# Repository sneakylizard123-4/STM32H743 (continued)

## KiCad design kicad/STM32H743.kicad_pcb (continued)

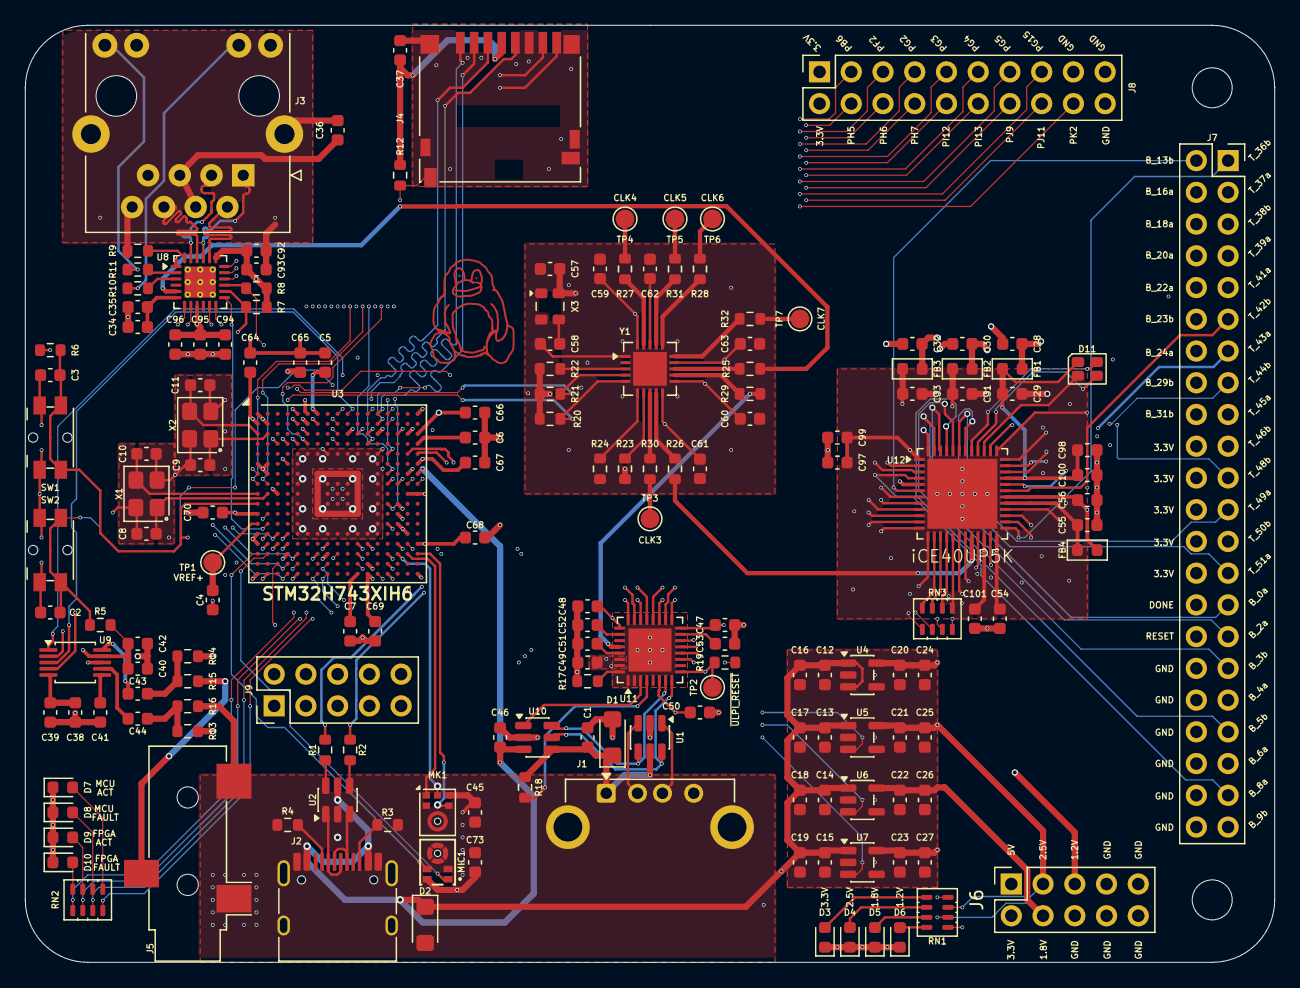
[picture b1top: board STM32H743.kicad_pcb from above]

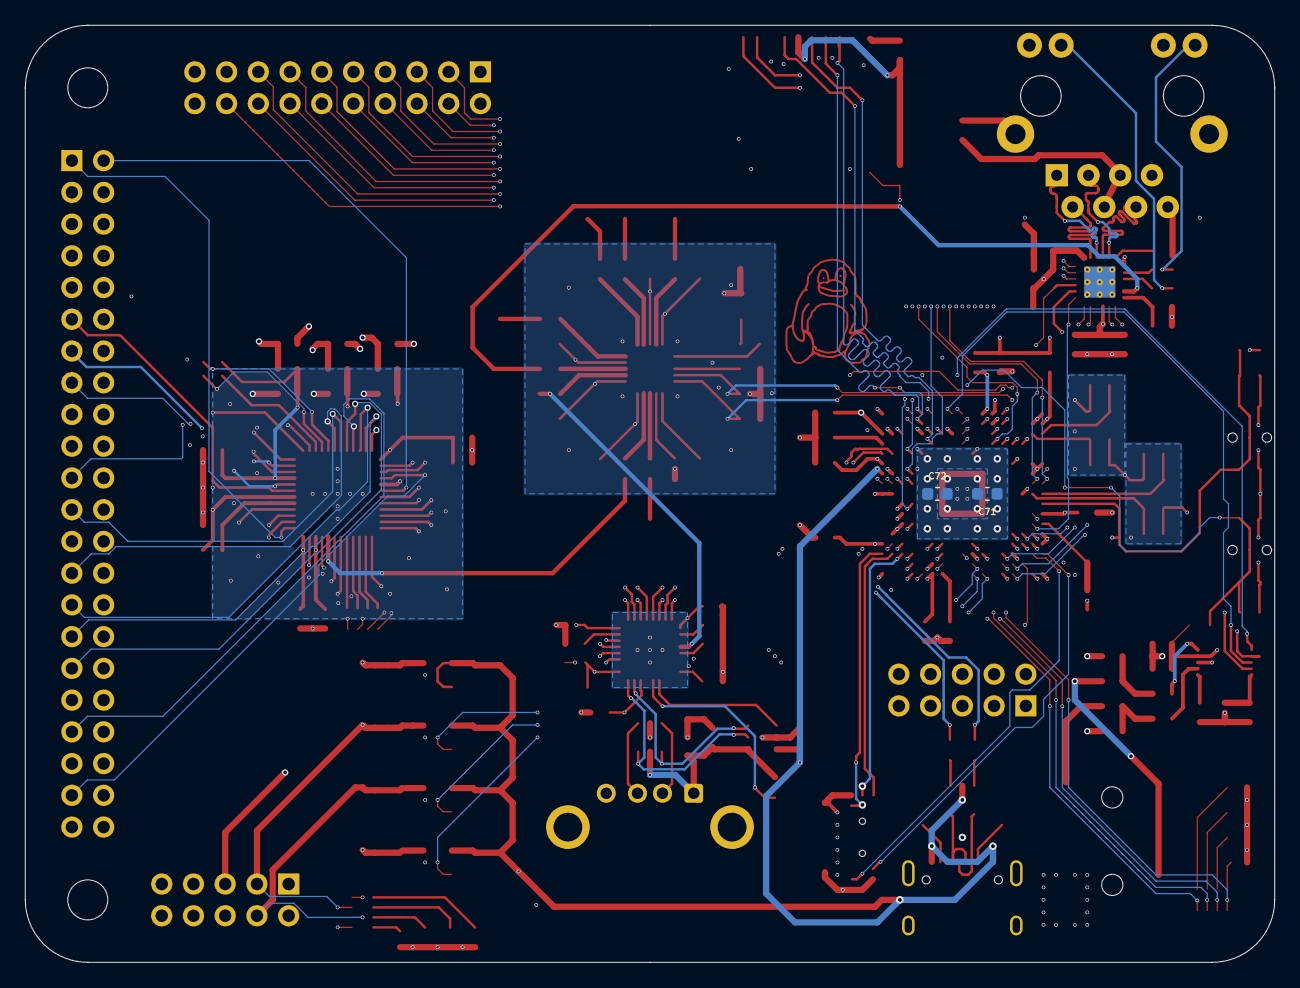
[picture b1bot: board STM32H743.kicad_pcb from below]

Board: 6 copper layers, 100.0 x 75.0 mm, 171 parts (2 on the bottom side), 196 nets.

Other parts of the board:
C73: 0.1uF; C_0603_1608Metric
MIC1: MMICT390200012; MIC-SMD_5P-L3.5-W2.7-TL_MMICT390200012
TP3, TP4, TP5, TP6, TP7: TestPoint; TestPoint_Pad_D1.5mm

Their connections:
+3.3V: C73.1, MIC1.5 (VDD); also elsewhere on the board
/Audio/DFSDM1.CKIN1: MIC1.4 (CLK); also elsewhere on the board
/Audio/DFSDM1.DATIN1: MIC1.1 (DATA); also elsewhere on the board
GND: C73.2, MIC1.3 (GND); also elsewhere on the board
unnamed 251: TP4.1 (1_1); also elsewhere on the board
unnamed 252: TP6.1 (1_1); also elsewhere on the board
unnamed 253: TP3.1 (1_1); also elsewhere on the board
unnamed 254: TP5.1 (1_1); also elsewhere on the board
unnamed 255: TP7.1 (1_1); also elsewhere on the board

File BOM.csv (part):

Comment,Designators,Footprint,Quantity,Supplier,Supplier Part,Unit Price (USD),Extended Price (USD),Supplier Link,Notes
"STM32H743XIH6","U3","TFBGA-265",1,"LCSC","C114407",25.9662,25.9662,"https://www.lcsc.com/product-detail/C114407.html","Main MCU, 480 MHz, 2 MB flash"
"ICE40UP5K-SG48I","U12","QFN-48-EP 7x7",1,"LCSC","C2678152",10.9007,10.9007,"https://www.lcsc.com/product-detail/C2678152.html","Substitute for obsolete ICE40UP5K-SG48ITR, same package"
"USB3300-EZK-TR","U11","QFN-32",1,"LCSC","C108383",1.4647,1.4647,"https://www.lcsc.com/product-detail/C108383.html","USB 2.0 HS ULPI PHY"
"LAN8742A-CZ-TR","U8","QFN-24-EP 4x4",1,"LCSC","C621424",1.4025,1.4025,"https://www.lcsc.com/product-detail/C621424.html","10/100 Ethernet PHY"
"CS4344-CZZR","U9","TSSOP-10",1,"LCSC","C8952",1.5154,1.5154,"https://www.lcsc.com/product-detail/C8952.html","Stereo I2S audio DAC"
"Si5351C-B-GM","Y1","QFN-20",1,"LCSC","C3608122",5.5527,5.5527,"https://www.lcsc.com/product-detail/C3608122.html","Clock generator"
"TLV75733PDBV","U4","SOT-23-5",1,"LCSC","C485517",0.2005,0.2005,"https://www.lcsc.com/product-detail/C485517.html","3.3 V LDO"
"TLV75725PDBV","U5","SOT-23-5",1,"LCSC","C2872563",0.2318,0.2318,"https://www.lcsc.com/product-detail/C2872563.html","2.5 V LDO"
"TLV75718PDBV","U6","SOT-23-5",1,"LCSC","C507270",0.2985,0.2985,"https://www.lcsc.com/product-detail/C507270.html","1.8 V LDO"
"TLV75712PDBV","U7","SOT-23-5",1,"LCSC","C1509296",0.3415,0.3415,"https://www.lcsc.com/product-detail/C1509296.html","1.2 V LDO"
"USBLC6-2SC6","U1 U2","SOT-23-6",2,"LCSC","C7519",0.1797,0.3594,"https://www.lcsc.com/product-detail/C7519.html","USB ESD protection"
"TPD3S014DBVR","U10","SOT-23-6",1,"LCSC","C87384",1.0327,1.0327,"https://www.lcsc.com/product-detail/C87384.html","USB-A host power switch and protection"
"ICS-43434","MK1","LGA-6 3.5x2.7",1,"LCSC","C5656610",4.6035,4.6035,"https://www.lcsc.com/product-detail/C5656610.html","PDM microphone"
"MMICT390200012","MIC1","LGA",1,"LCSC","C3171752",1.5613,1.5613,"https://www.lcsc.com/product-detail/C3171752.html","PDM microphone"
"CLMVC-FKA-CLBDGL7LBB79353","D11","PLCC-4",1,"Mouser","941-CLMVCFKACLBDGL7L",0.1400,0.1400,"https://www.mouser.ca/en/ProductDetail/Cree-LED/CLMVC-FKA-CL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","RGB LED, ABGR"
"0.1 uF 50 V X7R","C100 C101 C2 C3 C37 C39 C4 C42 C45 C46 C47 C48 C49 C50 C57 C59 C60 C61 C62 C63 C64 C65 C66 C67 C68 C69 C70 C71 C72 C73 C92 C93 C94 C95 C96 C97 C98 C99 C12 C13 C14 C15 C20 C21 C22 C23 C58","0603",47,"LCSC","C14663",0.0084,0.3948,"https://www.lcsc.com/product-detail/C14663.html","Includes both 0.1 uF and 100 nF values"
"10 uF 25 V X5R","C16 C17 C18 C19 C24 C25 C26 C27 C38 C41 C56","0603",11,"LCSC","C96446",0.0429,0.4719,"https://www.lcsc.com/product-detail/C96446.html",""
"1 uF 25 V X7R","C28 C29 C30 C31 C32 C33 C34 C40 C54 C55","0603",10,"LCSC","C29936",0.0177,0.1770,"https://www.lcsc.com/product-detail/C29936.html",""
"2.2 uF 25 V X7R","C5 C6 C7","0603",3,"LCSC","C99228",0.0567,0.1701,"https://www.lcsc.com/product-detail/C99228.html",""
"4.7 uF 25 V X5R","C51 C52 C53","0603",3,"LCSC","C69335",0.0428,0.1284,"https://www.lcsc.com/product-detail/C69335.html",""
"3.3 uF 25 V X5R","C43 C44","0603",2,"LCSC","C5360803",0.0142,0.0284,"https://www.lcsc.com/product-detail/C5360803.html",""
"22 nF 50 V X7R","C36","0603",1,"LCSC","C21122",0.0071,0.0071,"https://www.lcsc.com/product-detail/C21122.html",""
"470 pF 50 V C0G","C35","0603",1,"LCSC","C106211",0.0069,0.0069,"https://www.lcsc.com/product-detail/C106211.html",""
"12 pF 50 V C0G","C8 C10","0603",2,"LCSC","C38523",0.0112,0.0224,"https://www.lcsc.com/product-detail/C38523.html",""
"18 pF 50 V C0G","C9 C11","0603",2,"LCSC","C1647",0.0158,0.0316,"https://www.lcsc.com/product-detail/C1647.html",""
"47 uF 6.3 V X5R","C1","0603",1,"LCSC","C140782",0.1382,0.1382,"https://www.lcsc.com/product-detail/C140782.html","Rev A value was 120 uF, which does not fit 0603. This is below the USB 2.0 host 120 uF recommendation."
"12.1 k 1%","R9","0603",1,"LCSC","C22864",0.0015,0.0015,"https://www.lcsc.com/product-detail/C22864.html",""
"SMF12A","D1 D2","SOD-123FL",2,"LCSC","C19077506",0.0325,0.0650,"https://www.lcsc.com/product-detail/C19077506.html","TVS"
"1 k at 100 MHz ferrite","FB1 FB2 FB3 FB4","0603",4,"LCSC","C304312",0.0150,0.0600,"https://www.lcsc.com/product-detail/C304312.html",""
"Green LED","D3 D4 D5 D6","0603",4,"LCSC","C52675989",0.0035,0.0140,"https://www.lcsc.com/product-detail/C52675989.html",""
"Yellow LED","D7 D9","0603",2,"LCSC","C965802",0.0072,0.0144,"https://www.lcsc.com/product-detail/C965802.html",""
"Red LED","D8 D10","0603",2,"LCSC","C2286",0.0077,0.0154,"https://www.lcsc.com/product-detail/C2286.html",""
"1 k resistor array x4","RN1 RN2","0603x4",2,"LCSC","C20197",0.0104,0.0208,"https://www.lcsc.com/product-detail/C20197.html",""
"0 ohm resistor array x4","RN3","0603x4",1,"LCSC","C1952",0.0090,0.0090,"https://www.lcsc.com/product-detail/C1952.html",""
"22 ohm","R1 R2","0603",2,"LCSC","C23345",0.0017,0.0034,"https://www.lcsc.com/product-detail/C23345.html","USB series termination"
"330 ohm","R10 R11","0603",2,"LCSC","C23138",0.0020,0.0040,"https://www.lcsc.com/product-detail/C23138.html",""
"10 k","R5 R6 R7 R8 R12 R13 R14 R19 R22 R23 R24","0603",11,"LCSC","C25804",0.0022,0.0242,"https://www.lcsc.com/product-detail/C25804.html",""
"470 ohm","R15 R16","0603",2,"LCSC","C23179",0.0023,0.0046,"https://www.lcsc.com/product-detail/C23179.html",""
"12 k 1%","R17","0603",1,"LCSC","C22790",0.0031,0.0031,"https://www.lcsc.com/product-detail/C22790.html",""
"820 ohm","R18","0603",1,"LCSC","C23253",0.0015,0.0015,"https://www.lcsc.com/product-detail/C23253.html",""
"1.8 k","R20 R21","0603",2,"LCSC","C4177",0.0021,0.0042,"https://www.lcsc.com/product-detail/C4177.html",""
"0 ohm","R25 R26 R27 R28 R29 R30 R31 R32","0603",8,"LCSC","C21189",0.0022,0.0176,"https://www.lcsc.com/product-detail/C21189.html",""
"5.1 k","R3 R4","0603",2,"LCSC","C23186",0.0015,0.0030,"https://www.lcsc.com/product-detail/C23186.html","USB-C CC pulldowns"
"USB-A DS1095","J1","USB-A THT",1,"LCSC","C19944602",0.2097,0.2097,"https://www.lcsc.com/product-detail/C19944602.html","Connfly DS1095-WNM0"
"USB-C 16P","J2","USB-C SMD",1,"LCSC","C165948",0.1869,0.1869,"https://www.lcsc.com/product-detail/C165948.html","HRO TYPE-C-31-M-12"
"RJ45 with magnetics","J3","RJ45 horizontal",1,"Mouser","493-HFJ112450EL12RL",4.5000,4.5000,"https://www.mouser.ca/en/ProductDetail/HALO-Electronics/HFJ1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","Halo HFJ11-2450E-L12RL"
"microSD socket","J4","microSD SMD",1,"LCSC","C719027",1.1652,1.1652,"https://www.lcsc.com/product-detail/C719027.html","Hirose DM3D-SF"
"3.5 mm audio jack","J5","SJ-3523-SMT",1,"Mouser","490-SJ-3523-SMT-TR",0.8800,0.8800,"https://www.mouser.ca/en/ProductDetail/Same-Sky/SJ-3523-SMT-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","CUI SJ-3523-SMT-TR"
"2x5 socket","J6","2x5 2.54 mm",1,"LCSC","C492399",0.1149,0.1149,"https://www.lcsc.com/product-detail/C492399.html",""
"2x22 socket","J7","2x22 2.54 mm",1,"LCSC","C27985237",0.4010,0.4010,"https://www.lcsc.com/product-detail/C27985237.html",""
"2x10 socket","J8","2x10 2.54 mm",1,"LCSC","C2897411",0.3264,0.3264,"https://www.lcsc.com/product-detail/C2897411.html",""
"2x5 header","J9","2x5 2.54 mm",1,"LCSC","C492422",0.0662,0.0662,"https://www.lcsc.com/product-detail/C492422.html",""
"EVQ-PUM02K","SW1 SW2","SMD 4.7x4.5 mm",2,"Mouser","667-EVQ-PUM02K",0.5700,1.1400,"https://www.mouser.ca/en/ProductDetail/Panasonic-Industry/EV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","Panasonic tactile switch"
"25 MHz crystal","X1","3225 4-pad",1,"LCSC","C9006",0.0951,0.0951,"https://www.lcsc.com/product-detail/C9006.html","12 pF load"
"32.768 kHz crystal","X2","3215 2-pad",1,"LCSC","C32346",0.1709,0.1709,"https://www.lcsc.com/product-detail/C32346.html","Current PCB uses a 3225 4-pad footprint. Rev B must change the footprint to 3215 2-pad before ordering."
"25 MHz TCXO","X3","2520 4-pad",1,"LCSC","C48994904",0.4534,0.4534,"https://www.lcsc.com/product-detail/C48994904.html","3.3 V clipped sine, +/-0.5 ppm"
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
